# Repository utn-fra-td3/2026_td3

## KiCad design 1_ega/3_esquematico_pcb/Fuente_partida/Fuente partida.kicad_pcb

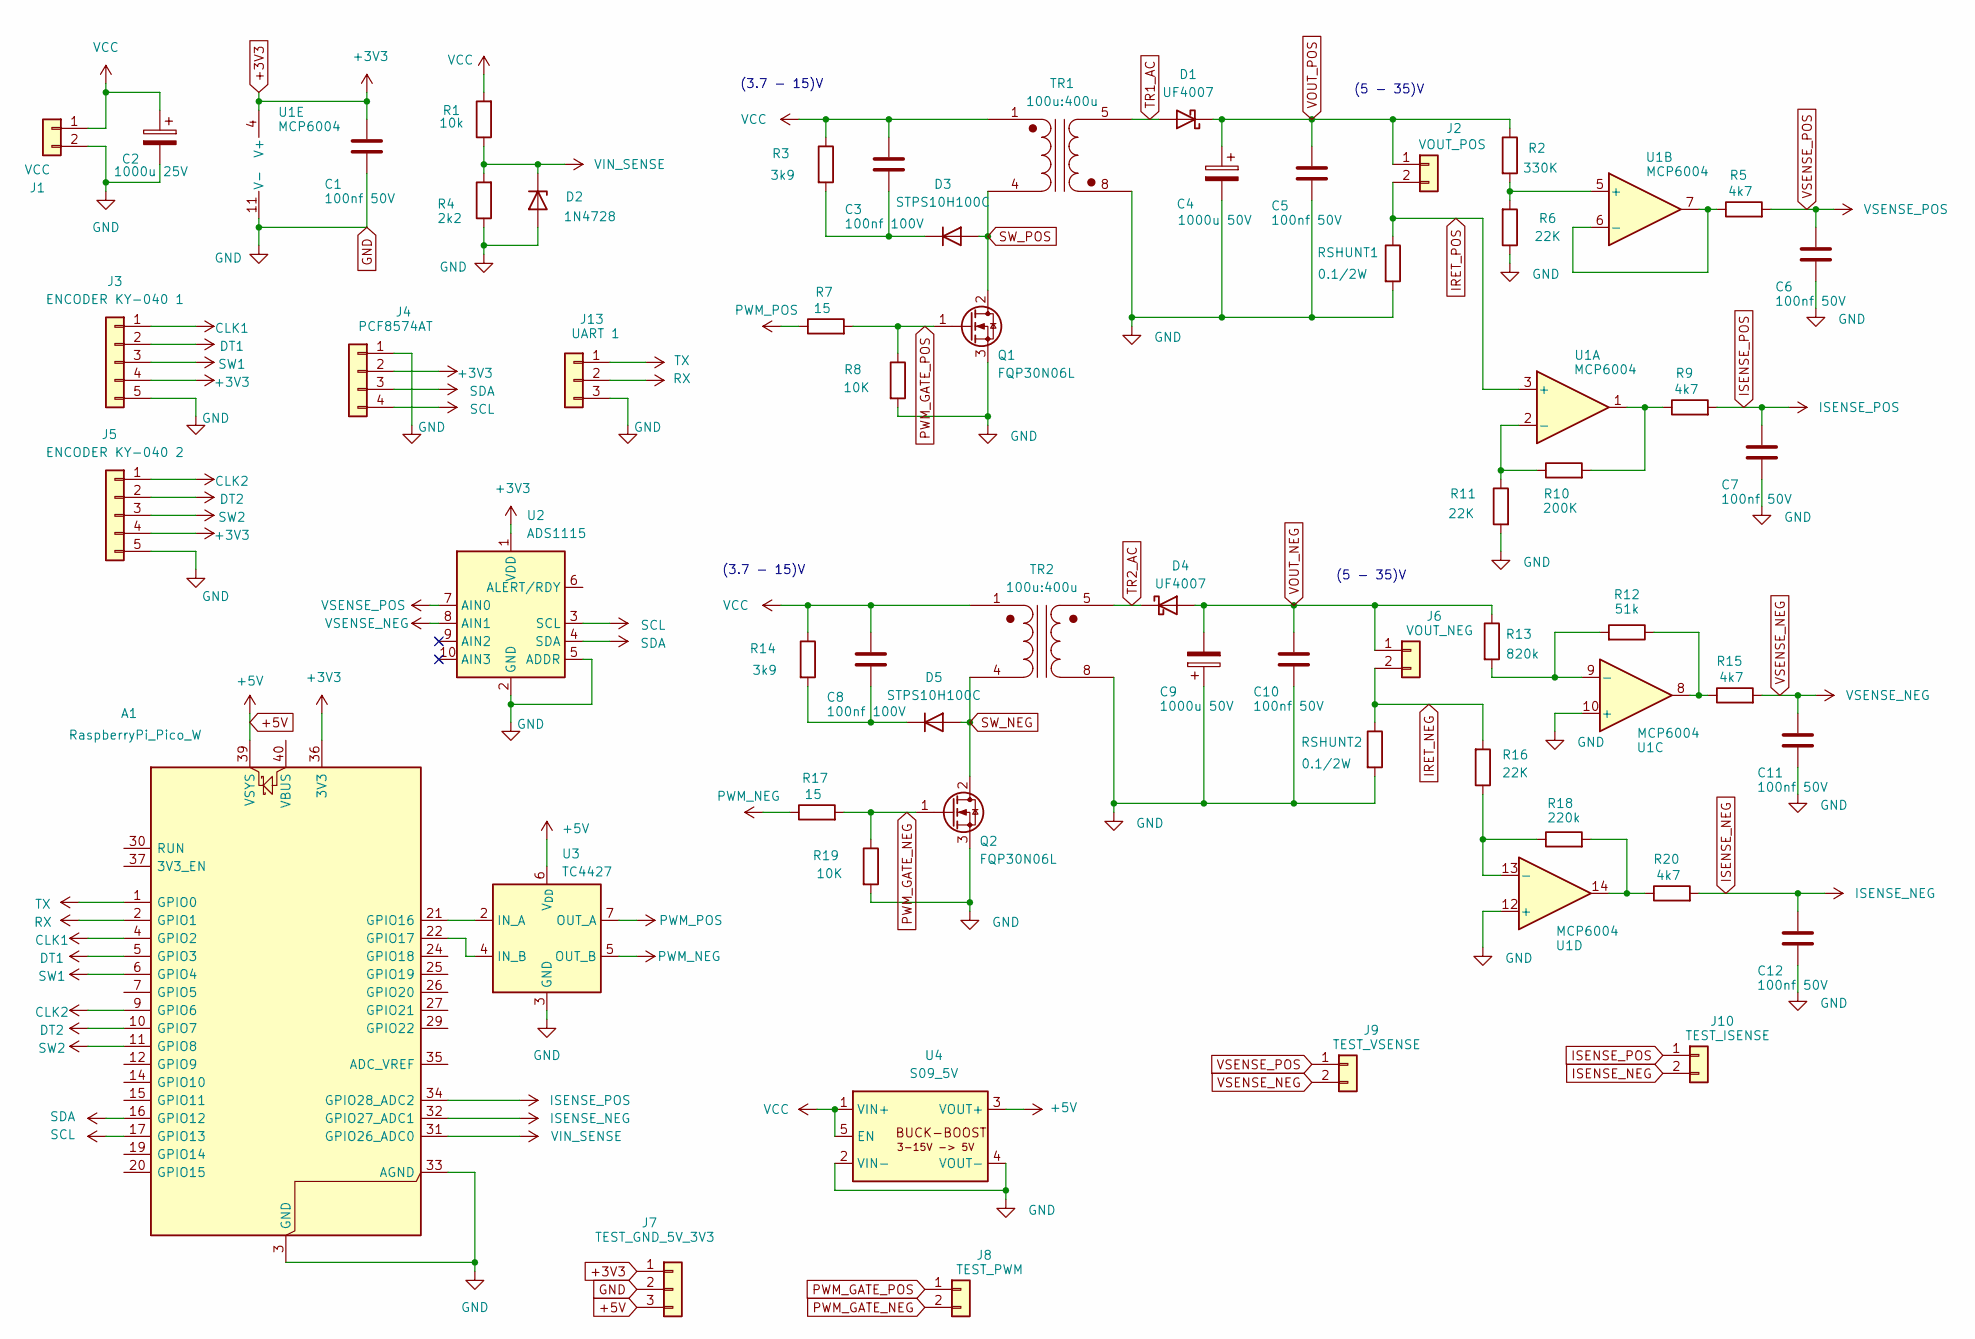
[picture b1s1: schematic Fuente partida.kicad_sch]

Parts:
A1: RaspberryPi_Pico_W; RaspberryPi_Pico_W_Pads_Anchos_Sin_Keepout_Antena
C1, C5, C6, C7, C10, C11, C12: 100nf 50V; C_Disc_D5.0mm_W2.5mm_P5.00mm
C2: 1000u 25V; CP_Radial_D10.0mm_P5.00mm
C3, C8: 100nf 100V; C_Disc_D5.0mm_W2.5mm_P5.00mm
C4, C9: 1000u 50V; CP_Radial_D16.0mm_P7.50mm
D1, D4: UF4007; D_DO-15_P10.16mm_Horizontal
D2: 1N4728; D_DO-41_SOD81_P10.16mm_Horizontal
D3, D5: STPS10H100C; D_DO-41_SOD81_P10.16mm_Horizontal
J1: VCC; TerminalBlock_MaiXu_MX126-5.0-02P_1x02_P5.00mm
J2: VOUT_POS; TerminalBlock_MaiXu_MX126-5.0-02P_1x02_P5.00mm
J3: ENCODER KY-040 1; PinSocket_1x05_P2.54mm_Vertical
J4: PCF8574AT; PinSocket_1x04_P2.54mm_Vertical
J5: ENCODER KY-040 2; PinSocket_1x05_P2.54mm_Vertical
J6: VOUT_NEG; TerminalBlock_MaiXu_MX126-5.0-02P_1x02_P5.00mm
J7: TEST_GND_5V_3V3; JST_XH_B3B-XH-A_1x03_P2.50mm_Vertical
J8: TEST_PWM; JST_XH_B2B-XH-A_1x02_P2.50mm_Vertical
J9: TEST_VSENSE; JST_XH_B2B-XH-A_1x02_P2.50mm_Vertical
J10: TEST_ISENSE; JST_XH_B2B-XH-A_1x02_P2.50mm_Vertical
J13: UART 1; PinSocket_1x03_P2.54mm_Vertical
Q1, Q2: FQP30N06L; TO-220-3_Vertical_P3.81mm
R1: 10k; R_Axial_DIN0204_L3.6mm_D1.6mm_P7.62mm_Horizontal
R2: 330K; R_Axial_DIN0204_L3.6mm_D1.6mm_P7.62mm_Horizontal
R3, R14: 3k9; R_Axial_DIN0204_L3.6mm_D1.6mm_P7.62mm_Horizontal
R4: 2k2; R_Axial_DIN0204_L3.6mm_D1.6mm_P7.62mm_Horizontal
R5, R9, R15, R20: 4k7; R_Axial_DIN0204_L3.6mm_D1.6mm_P7.62mm_Horizontal
R6, R11, R16: 22K; R_Axial_DIN0204_L3.6mm_D1.6mm_P7.62mm_Horizontal
R7, R17: 15; R_Axial_DIN0204_L3.6mm_D1.6mm_P7.62mm_Horizontal
R8, R19: 10K; R_Axial_DIN0204_L3.6mm_D1.6mm_P7.62mm_Horizontal
R10: 200K; R_Axial_DIN0204_L3.6mm_D1.6mm_P7.62mm_Horizontal
R12: 51k; R_Axial_DIN0204_L3.6mm_D1.6mm_P7.62mm_Horizontal
R13: 820k; R_Axial_DIN0204_L3.6mm_D1.6mm_P7.62mm_Horizontal
R18: 220k; R_Axial_DIN0204_L3.6mm_D1.6mm_P7.62mm_Horizontal
RSHUNT1, RSHUNT2: 0.1/2W; R_Axial_DIN0516_L15.5mm_D5.0mm_P7.62mm_Vertical
TR1, TR2: 100u:400u; Bobina_4P_30.5mm_P1_P4_P5_P8
U1: MCP6004; DIP-14_W7.62mm
U2: ADS1115; ADS1115_Modulo_1x10_Pads_Corregidos
U3: TC4427; DIP-8_W7.62mm
U4: S09_5V; S09_5V_BuckBoost_19x14mm

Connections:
+3V3: A1.36 (3V3), C1.1, J3.4, J4.2, J5.4, J7.1, U1.4 (V+), U2.1 (VDD)
+5V: A1.39 (VSYS), J7.3, U3.6 (V_{DD}), U4.3 (VOUT+)
CLK1: A1.4 (GPIO2), J3.1
CLK2: A1.9 (GPIO6), J5.1
DT1: A1.5 (GPIO3), J3.2
DT2: A1.10 (GPIO7), J5.2
GND: A1.3 (GND), A1.8 (GND), A1.13 (GND), A1.18 (GND), A1.23 (GND), A1.28 (GND), A1.33 (AGND), A1.38 (GND), C1.2, C2.2, C4.2, C5.2, C6.2, C7.2, C9.1, C10.2, C11.2, C12.2, D2.2 (A), J1.2, J3.5, J4.1, J5.5, J7.2, J13.3, Q1.3 (S), Q2.3 (S), R4.1, R6.1, R8.2, R11.2, R19.2, RSHUNT1.2, RSHUNT2.2, TR1.8 (SA), TR2.8 (SA), U1.10 (+), U1.11 (V-), U1.12 (+), U2.2 (GND), U2.5 (ADDR), U3.3 (GND), U4.2 (VIN-), U4.4 (VOUT-)
IRET_NEG: J6.2, R16.2, RSHUNT2.1
IRET_POS: J2.2, RSHUNT1.1, U1.3 (+)
ISENSE_NEG: A1.32 (GPIO27_ADC1), C12.1, J10.2, R20.2
ISENSE_POS: A1.34 (GPIO28_ADC2), C7.1, J10.1, R9.2
unnamed: A1.21 (GPIO16), U3.2 (IN_A)
unnamed: A1.22 (GPIO17), U3.4 (IN_B)
unnamed: C3.2, D3.1 (K), R3.2
unnamed: C8.2, D5.1 (K), R14.2
unnamed: R9.1, R10.2, U1.1
unnamed: R12.1, R15.1, U1.8
unnamed: R18.2, R20.1, U1.14
unnamed: R10.1, R11.1, U1.2 (-)
unnamed: R2.2, R6.2, U1.5 (+)
unnamed: R5.1, U1.6 (-), U1.7
unnamed: R12.2, R13.2, U1.9 (-)
unnamed: R16.1, R18.1, U1.13 (-)
PWM_GATE_NEG: J8.2, Q2.1 (G), R17.2, R19.1
PWM_GATE_POS: J8.1, Q1.1 (G), R7.2, R8.1
PWM_NEG: R17.1, U3.5 (OUT_B)
PWM_POS: R7.1, U3.7 (OUT_A)
RX: A1.2 (GPIO1), J13.2
SCL: A1.17 (GPIO13), J4.4, U2.3 (SCL)
SDA: A1.16 (GPIO12), J4.3, U2.4 (SDA)
SW1: A1.6 (GPIO4), J3.3
SW2: A1.11 (GPIO8), J5.3
SW_NEG: D5.2 (A), Q2.2 (D), TR2.4 (AB)
SW_POS: D3.2 (A), Q1.2 (D), TR1.4 (AB)
TR1_AC: D1.2 (A), TR1.5 (SB)
TR2_AC: D4.1 (K), TR2.5 (SB)
TX: A1.1 (GPIO0), J13.1
VCC: C2.1, C3.1, C8.1, J1.1, R1.2, R3.1, R14.1, TR1.1 (AA), TR2.1 (AA), U4.1 (VIN+), U4.5 (EN)
VIN_SENSE: A1.31 (GPIO26_ADC0), D2.1 (K), R1.1, R4.2
VOUT_NEG: C9.2, C10.1, D4.2 (A), J6.1, R13.1
VOUT_POS: C4.1, C5.1, D1.1 (K), J2.1, R2.1
VSENSE_NEG: C11.1, J9.2, R15.2, U2.8 (AIN1)
VSENSE_POS: C6.1, J9.1, R5.2, U2.7 (AIN0)

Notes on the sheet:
(5 - 35)V
(3.7 - 15)V

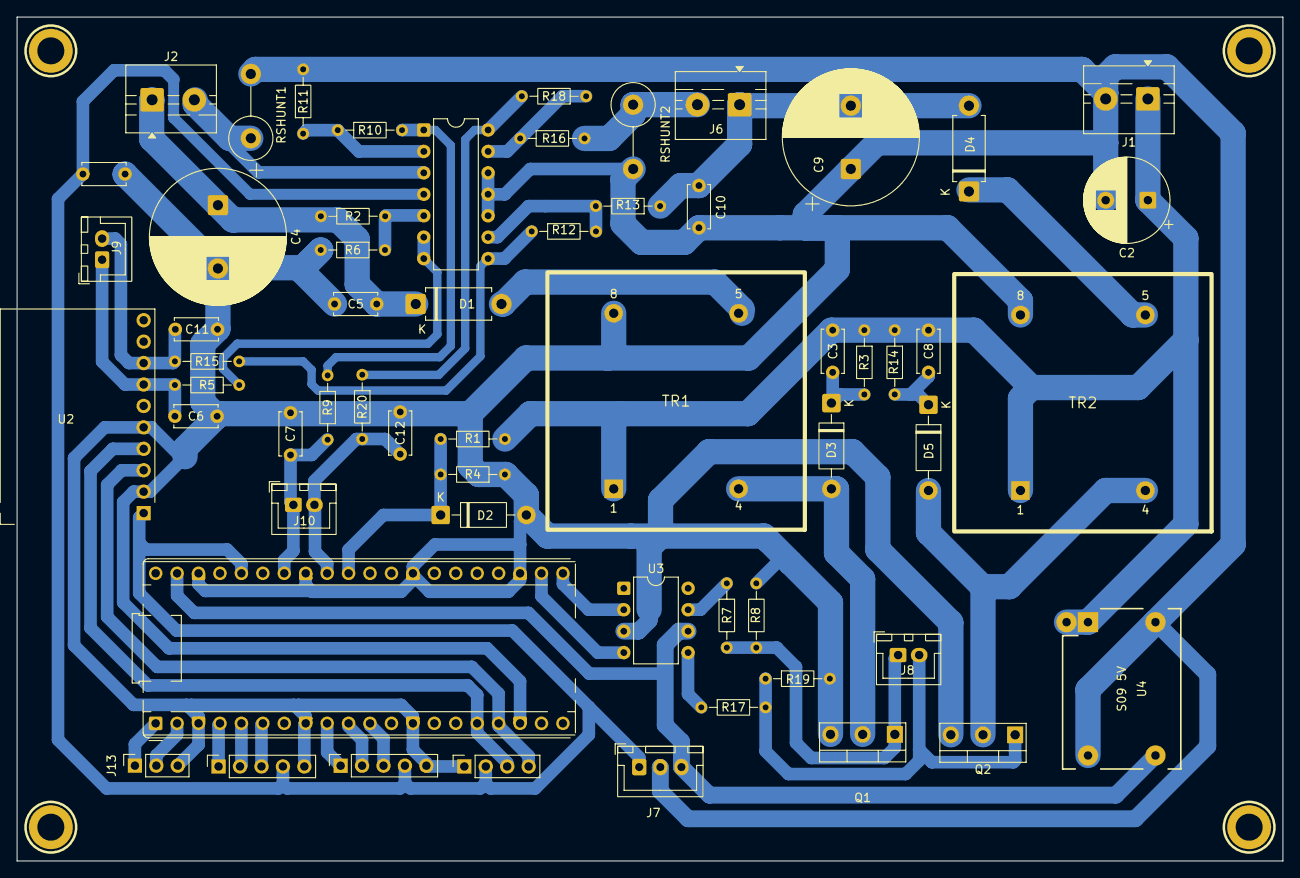
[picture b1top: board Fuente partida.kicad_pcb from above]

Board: 2 copper layers, 150.0 x 100.0 mm, 63 parts (0 on the bottom side), 43 nets.

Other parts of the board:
H1, H2, H3, H4: M3; MountingHole_3.2mm_M3_Pad_CNC

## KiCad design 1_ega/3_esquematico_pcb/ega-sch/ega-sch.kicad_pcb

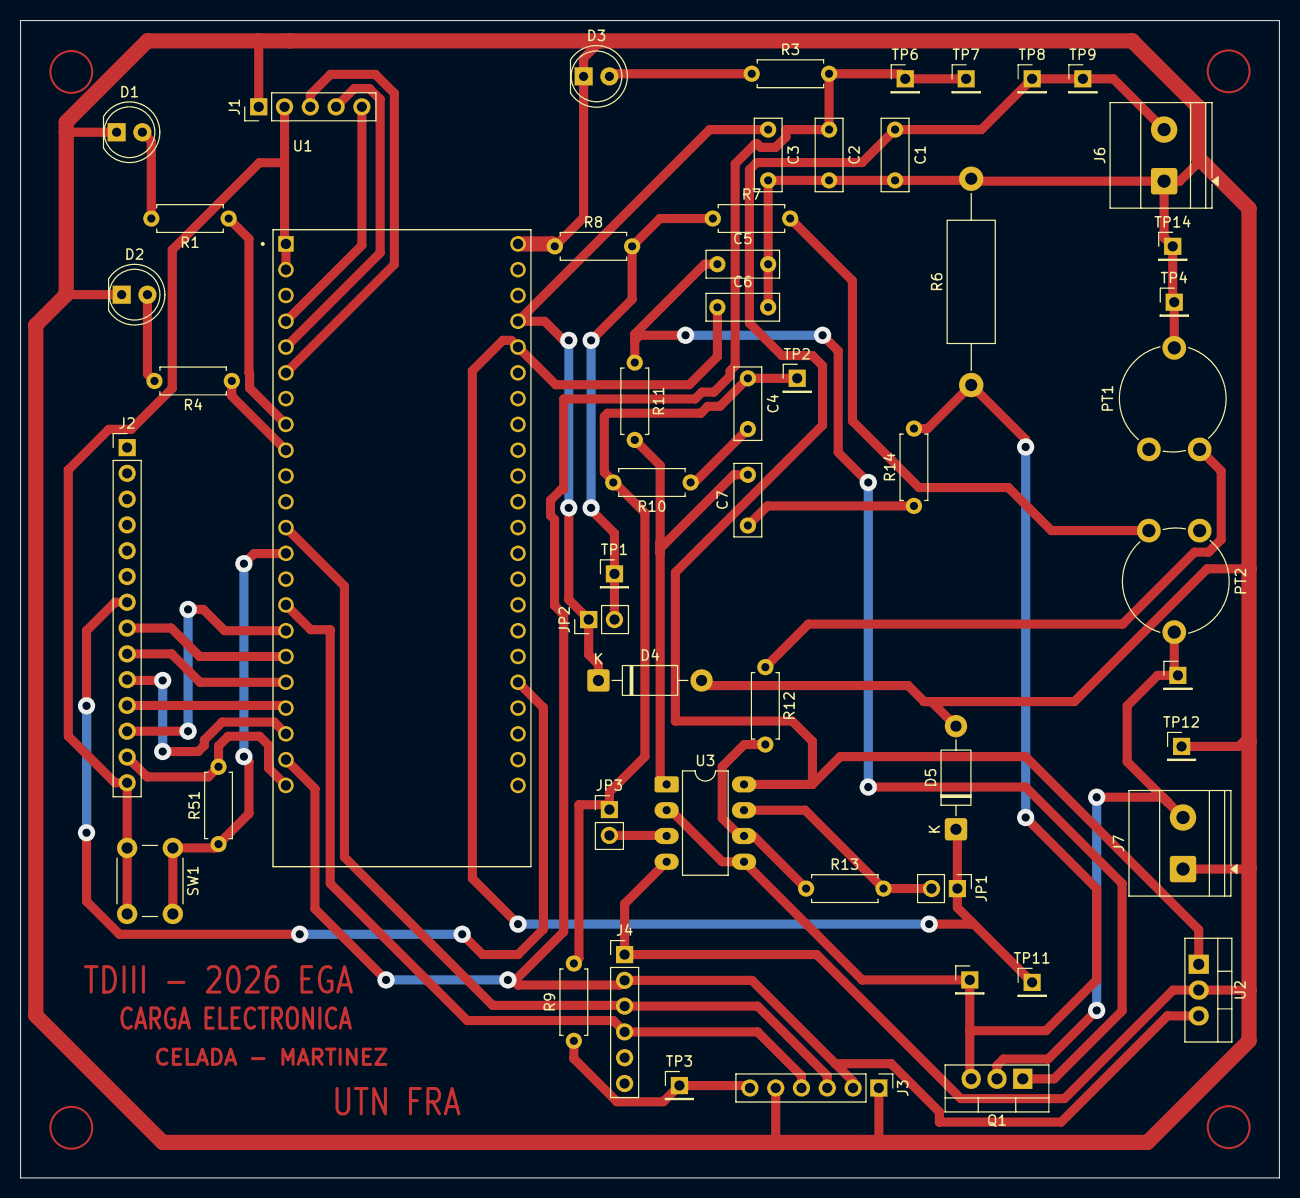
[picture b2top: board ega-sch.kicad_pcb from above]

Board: 2 copper layers, 124.0 x 114.0 mm, 54 parts (0 on the bottom side), 37 nets.

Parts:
C1, C2: 0,33uF; C_Disc_D7.0mm_W2.5mm_P5.00mm
C3, C4, C6: 100nF; C_Disc_D7.0mm_W2.5mm_P5.00mm
C5: 10nF; C_Disc_D7.0mm_W2.5mm_P5.00mm
C7: 1nF; C_Disc_D7.0mm_W2.5mm_P5.00mm
D1, D2: LD271; LED_D5.0mm_IRGrey
D3: ENCENDIDO; LED_D5.0mm_FlatTop
D4, D5: 1N4728A; D_DO-41_SOD81_P10.16mm_Horizontal
J1: Encoder; PinHeader_1x05_P2.54mm_Vertical
J2: TFT_Display; PinHeader_1x14_P2.54mm_Vertical
J3: MCP4725; PinHeader_1x06_P2.54mm_Vertical
J4: DS3231; PinHeader_1x06_P2.54mm_Vertical
J6: V+; TerminalBlock_Phoenix_MKDS-1,5-2-5.08_1x02_P5.08mm_Horizont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
J7: Ventrada; TerminalBlock_Phoenix_MKDS-1,5-2-5.08_1x02_P5.08mm_Horizont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
JP1, JP2, JP3: Jumper; PinHeader_1x02_P2.54mm_Vertical
PT1, PT2: PRESET 1K; Potentiometer_Piher_PT-10-V10_Vertical
Q1: IRFZ44; TO-220-3_Vertical
R1, R4: 330; R_Axial_DIN0207_L6.3mm_D2.5mm_P7.62mm_Horizontal
R3: 1K; R_Axial_DIN0207_L6.3mm_D2.5mm_P7.62mm_Horizontal
R6: Rshunt; R_Axial_DIN0414_L11.9mm_D4.5mm_P20.32mm_Horizontal
R7: 12K; R_Axial_DIN0207_L6.3mm_D2.5mm_P7.62mm_Horizontal
R8: 4,7K; R_Axial_DIN0207_L6.3mm_D2.5mm_P7.62mm_Horizontal
R9, R10, R12, R14, R51: 10K; R_Axial_DIN0207_L6.3mm_D2.5mm_P7.62mm_Horizontal
R11: 100; R_Axial_DIN0207_L6.3mm_D2.5mm_P7.62mm_Horizontal
R13: 3,3K; R_Axial_DIN0207_L6.3mm_D2.5mm_P7.62mm_Horizontal
SW1: SW_Push; SW_PUSH_6mm_H5mm
TP1: ADC_VIN; PinHeader_1x01_P2.54mm_Vertical
TP2: DAC; PinHeader_1x01_P2.54mm_Vertical
TP3: VDAC; PinHeader_1x01_P2.54mm_Vertical
TP4, TP14: GND; PinHeader_1x01_P2.54mm_Vertical
TP5: VIN; PinHeader_1x01_P2.54mm_Vertical
TP6, TP7: +5V; PinHeader_1x01_P2.54mm_Vertical
TP8, TP9: +12V; PinHeader_1x01_P2.54mm_Vertical
TP10: VSENS; PinHeader_1x01_P2.54mm_Vertical
TP11: ADC_VSENS; PinHeader_1x01_P2.54mm_Vertical
TP12: GND2; PinHeader_1x01_P2.54mm_Vertical
U1: ESP32-S3-DEVKITC-1-N16R8V; XCVR_ESP32-S3-DEVKITC-1-N16R8V
U2: LM7805_TO220; TO-220-3_Vertical
U3: LM358; DIP-8_W7.62mm_LongPads

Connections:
+3V3: J1.2, J2.14, SW1.2, U1.J1_1 (3V3), U1.J1_2 (3V3)
+5V: C2.1, J3.2, J4.2, R3.2, TP6.1, TP7.1, U1.J1_21 (5V0), U2.3 (VO)
+12V: C1.1, J6.2, TP8.1, TP9.1, U2.1 (VI), U3.8 (V+)
/Vin: J7.2, PT2.2, Q1.2 (D), TP5.1
ADC_VIN: C3.1, D4.1 (K), JP2.1 (A), U1.J3_4 (GPIO1)
ADC_VSENS: C6.1, D5.1 (K), JP1.1 (A), TP11.1, U1.J3_5 (GPIO2)
CLK: J1.5, U1.J1_4 (GPIO4)
DAC: J3.6, R9.1, TP3.1
DT: J1.4, U1.J1_5 (GPIO5)
GND: C1.2, C2.2, C3.2, C5.2, C6.2, D1.1 (K), D2.1 (K), D3.1 (K), D4.2 (A), D5.2 (A), J1.1, J2.13, J3.1, J3.5, J4.1, J6.1, J7.1, PT1.2, R6.2, R8.1, R51.2, TP4.1, TP12.1, TP14.1, U1.J1_22 (GND), U1.J3_1 (GND), U1.J3_21 (GND), U1.J3_22 (GND), U2.2 (GND), U3.4 (V-)
GND2: C4.2, R10.1
I2C0_SCL: J3.4, J4.4, U1.J1_15 (GPIO9)
I2C0_SDA: J3.3, J4.3, U1.J1_12 (GPIO8)
LED_MAX: R4.1, U1.J1_9 (GPIO16)
LED_MIN: R1.1, U1.J1_8 (GPIO15)
unnamed: C7.1, R14.1
unnamed: C7.2, R11.2, U3.1
unnamed: D1.2 (A), R1.2
unnamed: D2.2 (A), R4.2
unnamed: D3.2 (A), R3.1
unnamed: JP1.2 (B), R13.2, U3.7
unnamed: JP2.2 (B), R7.1, R8.2, TP1.1
unnamed: C4.1, JP3.1 (A), R9.2, R10.2, TP2.1
unnamed: JP3.2 (B), U3.3 (+)
unnamed: PT1.1, R12.1
unnamed: PT2.1, R7.2
unnamed: C5.1, Q1.1 (G), R11.1
unnamed: Q1.3 (S), R6.1, R14.2, TP10.1, U3.2 (-), U3.5 (+)
unnamed: R12.2, R13.1, U3.6 (-)
SW: J1.3, U1.J1_6 (GPIO6)
SW_CONFIG: R51.1, SW1.1, U1.J1_13 (GPIO3)
TFT_CS: J2.12, U1.J1_16 (GPIO10)
TFT_DC: J2.10, U1.J1_20 (GPIO14)
TFT_LED: J2.7, U1.J3_18 (GPIO21)
TFT_RESET: J2.11, U1.J1_19 (GPIO13)
TFT_SCK: J2.8, U1.J1_17 (GPIO11)
TFT_SDI: J2.9, U1.J1_18 (GPIO12)

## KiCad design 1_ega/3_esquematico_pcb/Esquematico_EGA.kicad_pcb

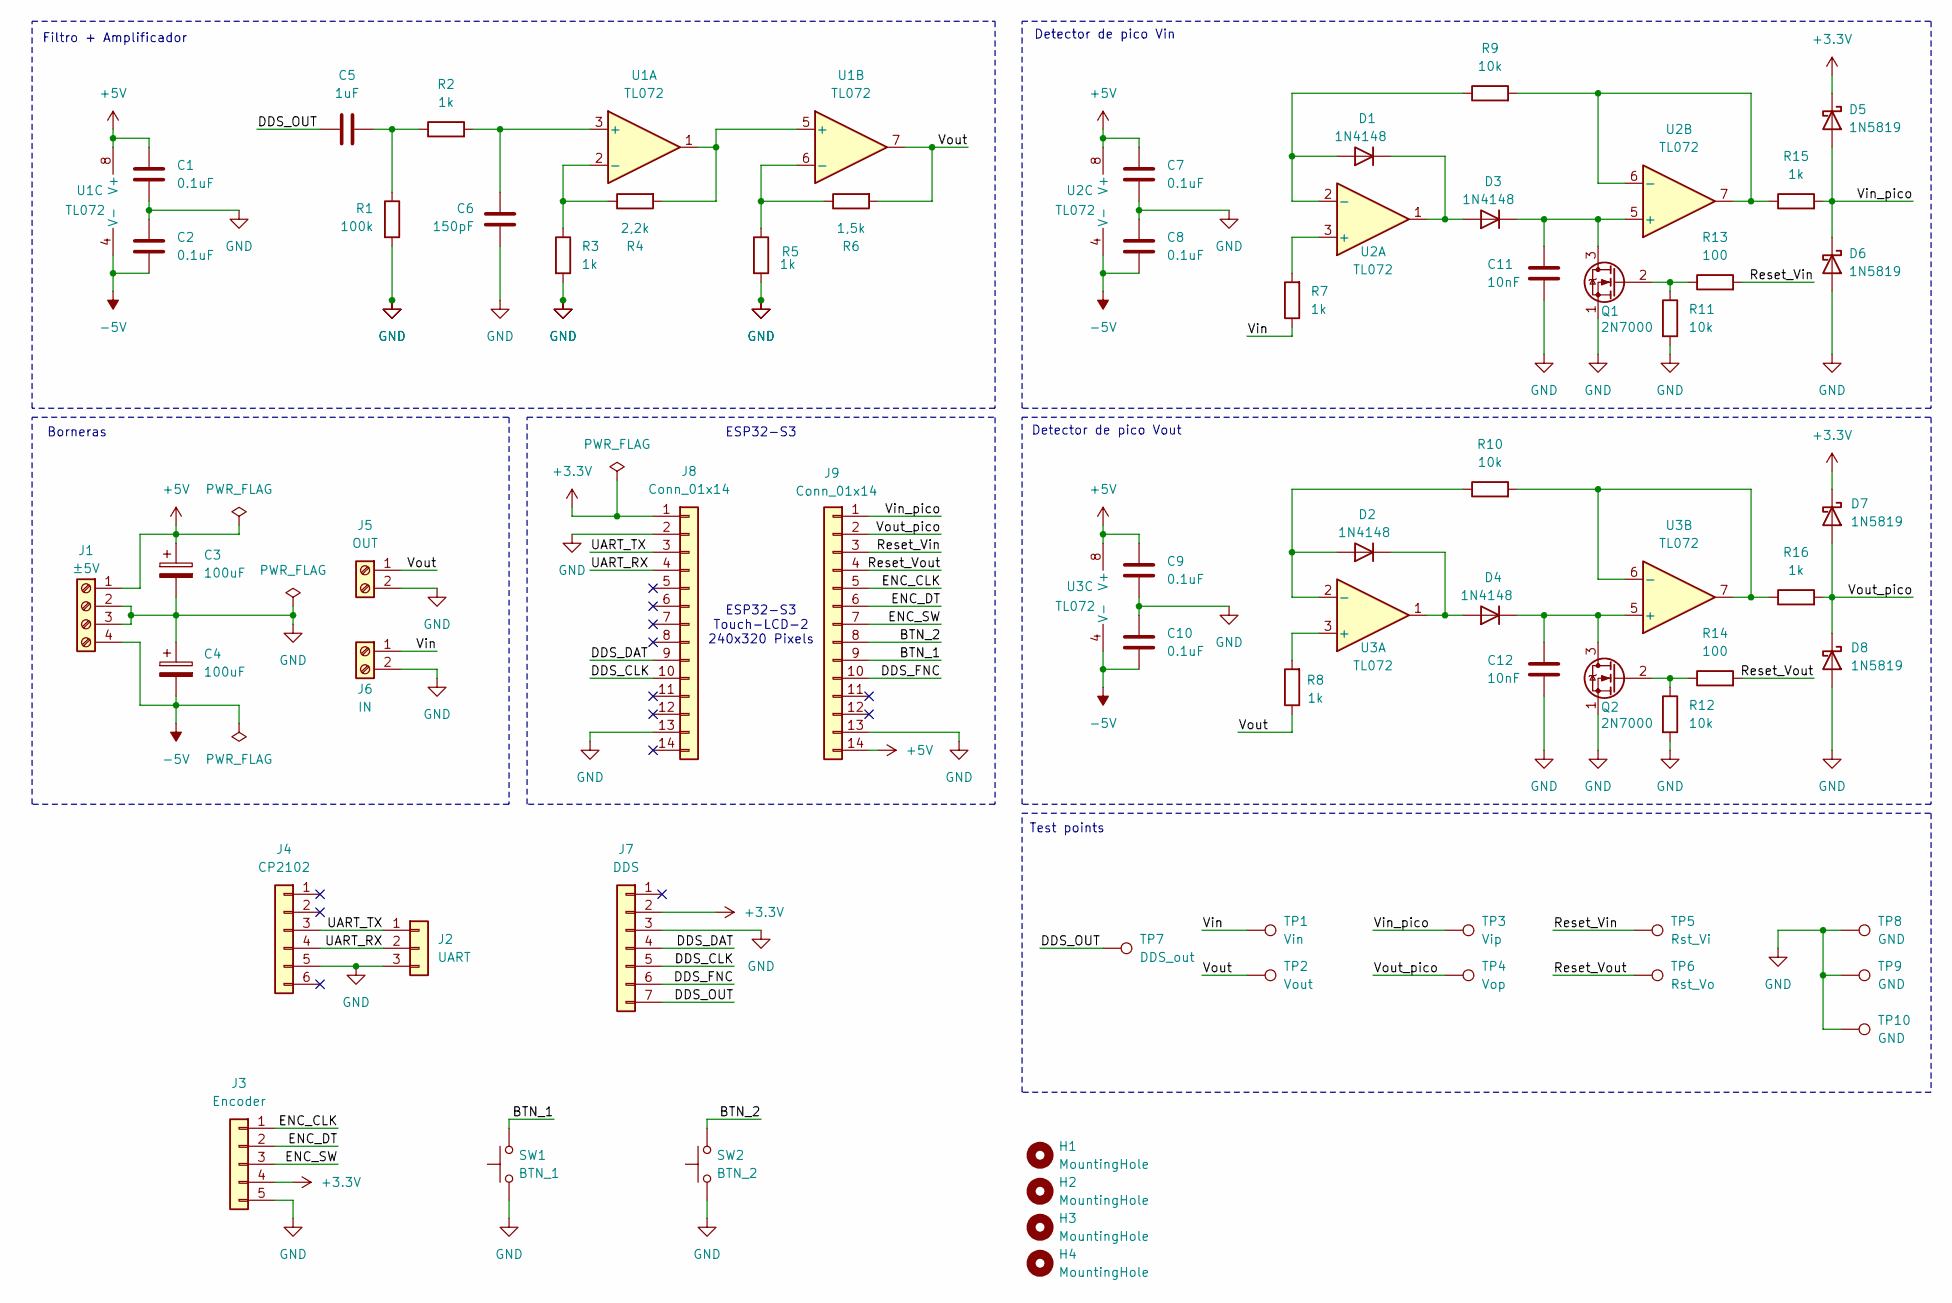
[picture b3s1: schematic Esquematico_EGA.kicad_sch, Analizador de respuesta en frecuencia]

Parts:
C1, C2, C7, C8, C9, C10: 0.1uF; C_Disc_D5.0mm_W2.5mm_P2.50mm
C3, C4: 100uF; CP_Radial_D7.5mm_P2.50mm
C5: 1uF; C_Disc_D5.0mm_W2.5mm_P5.00mm
C6: 150pF; C_Disc_D5.0mm_W2.5mm_P2.50mm
C11, C12: 10nF; C_Disc_D5.0mm_W2.5mm_P5.00mm
D1, D2, D3, D4: 1N4148; D_DO-35_SOD27_P7.62mm_Horizontal
D5, D6, D7, D8: 1N5819; D_DO-41_SOD81_P10.16mm_Horizontal
H1, H2, H3, H4: MountingHole; MountingHole_3.2mm_M3
J1: ±5V; TerminalBlock_Phoenix_MKDS-1,5-4-5.08_1x04_P5.08mm_Horizont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
J2: UART; PinSocket_1x03_P2.54mm_Vertical
J3: Encoder; PinSocket_1x05_P2.54mm_Vertical
J4: CP2102; PinSocket_1x06_P2.54mm_Vertical
J5: OUT; TerminalBlock_Phoenix_MKDS-1,5-2-5.08_1x02_P5.08mm_Horizont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
J6: IN; TerminalBlock_Phoenix_MKDS-1,5-2-5.08_1x02_P5.08mm_Horizont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
J7: DDS; PinSocket_1x07_P2.54mm_Vertical
J8, J9: Conn_01x14; PinSocket_1x14_P2.54mm_Vertical
Q1, Q2: 2N7000; TO-92_Inline_Wide
R1: 100k; R_Axial_DIN0207_L6.3mm_D2.5mm_P10.16mm_Horizontal
R2, R3, R5, R7, R8, R15, R16: 1k; R_Axial_DIN0207_L6.3mm_D2.5mm_P10.16mm_Horizontal
R4: 2,2k; R_Axial_DIN0207_L6.3mm_D2.5mm_P10.16mm_Horizontal
R6: 1,5k; R_Axial_DIN0207_L6.3mm_D2.5mm_P10.16mm_Horizontal
R9, R10, R11, R12: 10k; R_Axial_DIN0207_L6.3mm_D2.5mm_P10.16mm_Horizontal
R13, R14: 100; R_Axial_DIN0207_L6.3mm_D2.5mm_P10.16mm_Horizontal
SW1: BTN_1; SW_PUSH_6mm_H5mm
SW2: BTN_2; SW_PUSH_6mm_H5mm
TP1: Vin; PinHeader_1x01_P2.54mm_Vertical
TP2: Vout; PinHeader_1x01_P2.54mm_Vertical
TP3: Vip; PinHeader_1x01_P2.54mm_Vertical
TP4: Vop; PinHeader_1x01_P2.54mm_Vertical
TP5: Rst_Vi; PinHeader_1x01_P2.54mm_Vertical
TP6: Rst_Vo; PinHeader_1x01_P2.54mm_Vertical
TP7: DDS_out; PinHeader_1x01_P2.54mm_Vertical
TP8, TP9, TP10: GND; PinHeader_1x01_P2.54mm_Vertical
U1, U2, U3: TL072; DIP-8_W7.62mm_LongPads

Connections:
+3.3V: D5.1 (K), D7.1 (K), J3.4, J7.2, J8.1
+5V: C1.1, C3.1, C7.1, C9.1, J1.1, J9.14, U1.8 (V+), U2.8 (V+), U3.8 (V+)
-5V: C2.2, C4.2, C8.2, C10.2, J1.4, U1.4 (V-), U2.4 (V-), U3.4 (V-)
/BTN_1: J9.9, SW1.2
/BTN_2: J9.8, SW2.2
/DDS_CLK: J7.5, J8.10
/DDS_DAT: J7.4, J8.9
/DDS_FNC: J7.6, J9.10
/DDS_OUT: C5.1, J7.7, TP7.1 (1_1)
/ENC_CLK: J3.1, J9.5
/ENC_DT: J3.2, J9.6
/ENC_SW: J3.3, J9.7
/Reset_Vin: J9.3, R13.2, TP5.1 (1_1)
/Reset_Vout: J9.4, R14.2, TP6.1 (1_1)
/UART_RX: J2.2, J4.4, J8.4
/UART_TX: J2.1, J4.3, J8.3
/Vin: J6.1, R7.1, TP1.1 (1_1)
/Vin_pico: D5.2 (A), D6.1 (K), J9.1, R15.2, TP3.1 (1_1)
/Vout: J5.1, R6.2, R8.1, TP2.1 (1_1), U1.7
/Vout_pico: D7.2 (A), D8.1 (K), J9.2, R16.2, TP4.1 (1_1)
GND: C1.2, C2.1, C3.2, C4.1, C6.2, C7.2, C8.1, C9.2, C10.1, C11.2, C12.2, D6.2 (A), D8.2 (A), J1.2, J1.3, J2.3, J3.5, J4.5, J5.2, J6.2, J7.3, J8.2, J8.13, J9.13, Q1.1 (S), Q2.1 (S), R1.2, R3.2, R5.2, R11.2, R12.2, SW1.1, SW2.1, TP8.1 (1_1), TP9.1 (1_1), TP10.1 (1_1)
unnamed: C5.2, R1.1, R2.1
unnamed: D1.2 (A), R9.1, U2.2 (-)
unnamed: D1.1 (K), D3.2 (A), U2.1
unnamed: D2.2 (A), R10.1, U3.2 (-)
unnamed: D2.1 (K), D4.2 (A), U3.1
unnamed: C11.1, D3.1 (K), Q1.3 (D), U2.5 (+)
unnamed: C12.1, D4.1 (K), Q2.3 (D), U3.5 (+)
unnamed: Q1.2 (G), R11.1, R13.1
unnamed: Q2.2 (G), R12.1, R14.1
unnamed: C6.1, R2.2, U1.3 (+)
unnamed: R3.1, R4.1, U1.2 (-)
unnamed: R4.2, U1.1, U1.5 (+)
unnamed: R5.1, R6.1, U1.6 (-)
unnamed: R7.2, U2.3 (+)
unnamed: R9.2, R15.1, U2.6 (-), U2.7
unnamed: R8.2, U3.3 (+)
unnamed: R10.2, R16.1, U3.6 (-), U3.7

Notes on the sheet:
Filtro + Amplificador
ESP32-S3
Borneras
Detector de pico Vout
ESP32-S3 Touch-LCD-2 240x320 Pixels
Test points
Detector de pico Vin

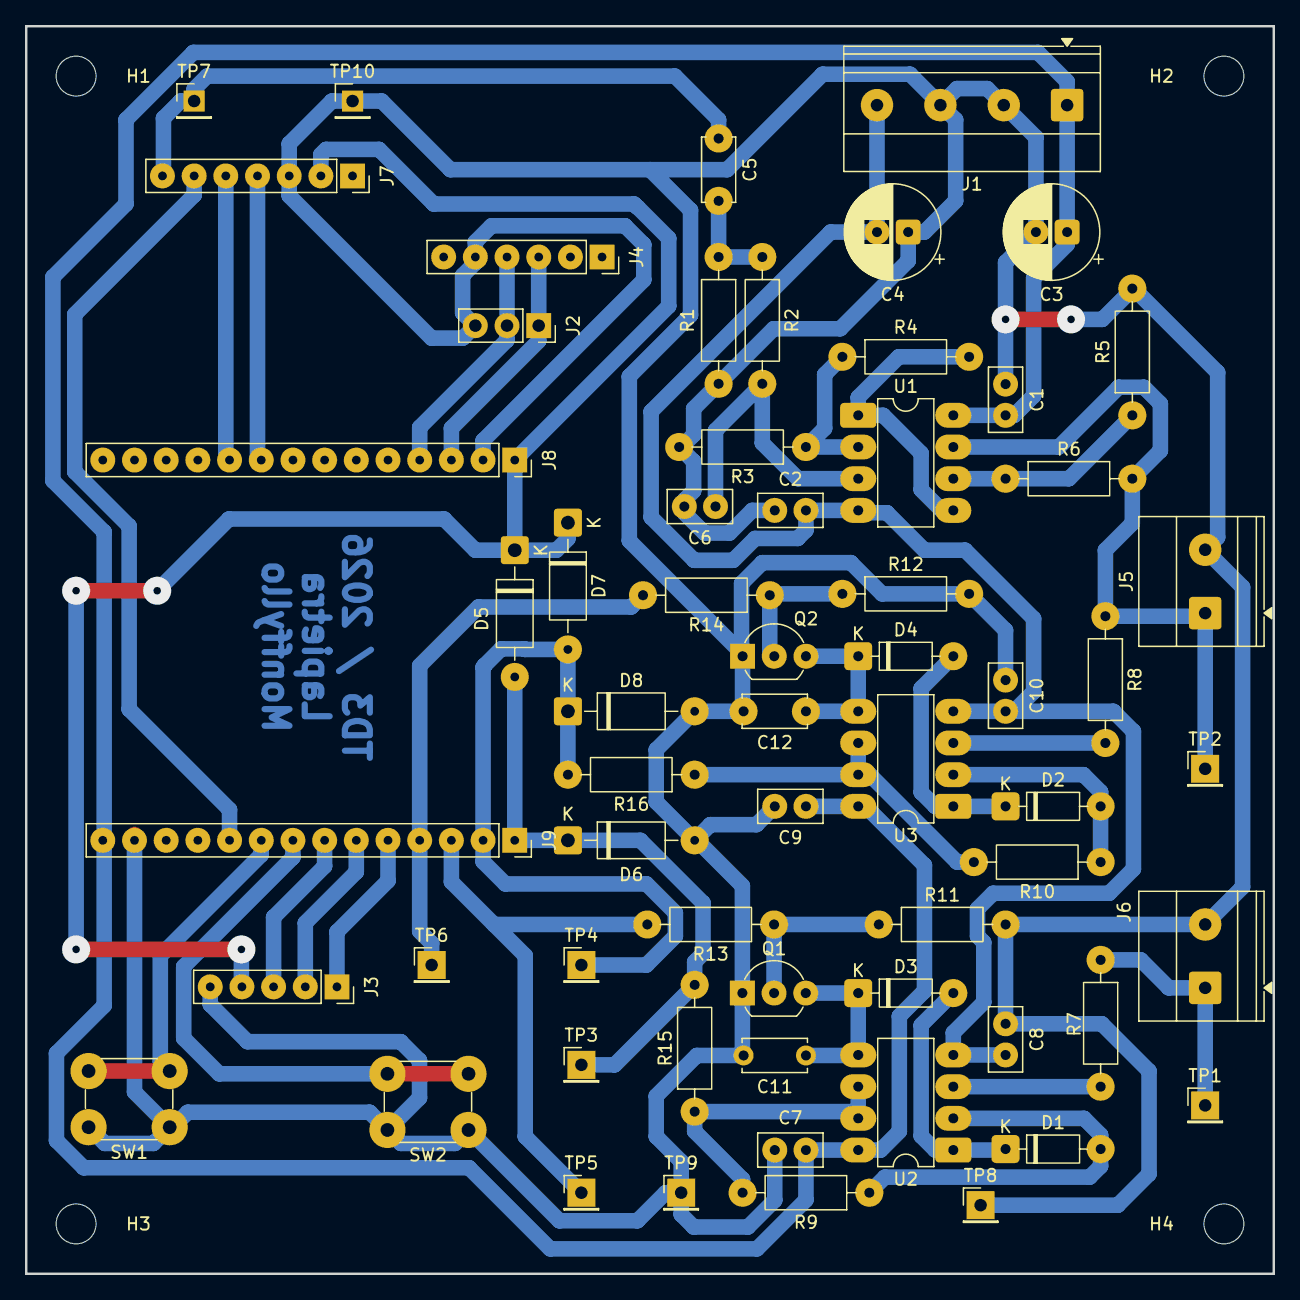
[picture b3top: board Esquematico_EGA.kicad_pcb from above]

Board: 2 copper layers, 100.0 x 100.0 mm, 66 parts (0 on the bottom side), 38 nets.

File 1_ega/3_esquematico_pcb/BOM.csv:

"Reference","Qty","Value","Footprint"
"C1,C2,C7,C8,C9,C10","6","0.1uF","Capacitor_THT:C_Disc_D5.0mm_W2.5mm_P2.50mm"
"C3,C4","2","100uF","Capacitor_THT:CP_Radial_D7.5mm_P2.50mm"
"C5","1","1uF","Capacitor_THT:C_Disc_D5.0mm_W2.5mm_P5.00mm"
"C6","1","150pF","Capacitor_THT:C_Disc_D5.0mm_W2.5mm_P2.50mm"
"C11,C12","2","10uF","Capacitor_THT:C_Disc_D5.0mm_W2.5mm_P5.00mm"
"D1,D2,D3,D4","4","1N4148","Diode_THT:D_DO-35_SOD27_P7.62mm_Horizontal"
"D5,D6,D7,D8","4","1N5819","Diode_THT:D_DO-41_SOD81_P10.16mm_Horizontal"
"J1","1","±5V","TerminalBlock_Phoenix:TerminalBlock_Phoenix_MKDS-1,5-4-5.08_1x04_P5.08mm_Horizontal"
"J2","1","UART","Connector_PinSocket_2.54mm:PinSocket_1x03_P2.54mm_Vertical"
"J3","1","Encoder","Connector_PinSocket_2.54mm:PinSocket_1x05_P2.54mm_Vertical"
"J4","1","CP2102","Connector_PinSocket_2.54mm:PinSocket_1x06_P2.54mm_Vertical"
"J5","1","OUT","TerminalBlock_Phoenix:TerminalBlock_Phoenix_MKDS-1,5-2-5.08_1x02_P5.08mm_Horizontal"
"J6","1","IN","TerminalBlock_Phoenix:TerminalBlock_Phoenix_MKDS-1,5-2-5.08_1x02_P5.08mm_Horizontal"
"J7","1","DDS","Connector_PinSocket_2.54mm:PinSocket_1x07_P2.54mm_Vertical"
"J8,J9","2","Conn_01x14","Connector_PinSocket_2.54mm:PinSocket_1x14_P2.54mm_Vertical"
"Q1,Q2","2","2N7000","Package_TO_SOT_THT:TO-92_Inline_Wide"
"R1","1","100k","Resistor_THT:R_Axial_DIN0207_L6.3mm_D2.5mm_P10.16mm_Horizontal"
"R2,R3,R5,R7,R8,R15,R16","7","1k","Resistor_THT:R_Axial_DIN0207_L6.3mm_D2.5mm_P10.16mm_Horizontal"
"R4","1","2,2k","Resistor_THT:R_Axial_DIN0207_L6.3mm_D2.5mm_P10.16mm_Horizontal"
"R6","1","1,5k","Resistor_THT:R_Axial_DIN0207_L6.3mm_D2.5mm_P10.16mm_Horizontal"
"R9,R10,R11,R12","4","10k","Resistor_THT:R_Axial_DIN0207_L6.3mm_D2.5mm_P10.16mm_Horizontal"
"R13,R14","2","100","Resistor_THT:R_Axial_DIN0207_L6.3mm_D2.5mm_P10.16mm_Horizontal"
"SW1","1","BTN_1","Button_Switch_THT:SW_PUSH_6mm_H5mm"
"SW2","1","BTN_2","Button_Switch_THT:SW_PUSH_6mm_H5mm"
"TP1","1","Vin","Connector_PinHeader_2.54mm:PinHeader_1x01_P2.54mm_Vertical"
"TP2","1","Vout","Connector_PinHeader_2.54mm:PinHeader_1x01_P2.54mm_Vertical"
"TP3","1","Vip","Connector_PinHeader_2.54mm:PinHeader_1x01_P2.54mm_Vertical"
"TP4","1","Vop","Connector_PinHeader_2.54mm:PinHeader_1x01_P2.54mm_Vertical"
"TP5","1","Rst_Vi","Connector_PinHeader_2.54mm:PinHeader_1x01_P2.54mm_Vertical"
"TP6","1","Rst_Vo","Connector_PinHeader_2.54mm:PinHeader_1x01_P2.54mm_Vertical"
"TP7","1","DDS_out","Connector_PinHeader_2.54mm:PinHeader_1x01_P2.54mm_Vertical"
"TP8,TP9,TP10","3","GND","Connector_PinHeader_2.54mm:PinHeader_1x01_P2.54mm_Vertical"
"U1,U2,U3","3","TL072","Package_DIP:DIP-8_W7.62mm_LongPads"

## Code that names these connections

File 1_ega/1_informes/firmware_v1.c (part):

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#define PIN_SPI_CLK      14
#define PIN_SPI_CS       15

#define PIN_ENC_CLK      18
#define PIN_ENC_DT       5
#define PIN_ENC_SW       19   // Botón Encoder: Cambia el PASO de frecuencia
#define PIN_BOTON_MODO   4    // Botón Extra: Cambia la FORMA de onda

#define PIN_I2C_SCL      22
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// UART Configuración (Nativa para Comandos Remotos)
#define UART_PORT_NUM      UART_NUM_0
#define UART_BUF_SIZE      1024
#define PIN_UART_TX        UART_PIN_NO_CHANGE
#define PIN_UART_RX        UART_PIN_NO_CHANGE

// Parámetros DDS
#define SAMPLING_FREQ      25000      
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static void IRAM_ATTR encoder_gpio_isr_handler(void* arg) {
    uint32_t tiempo_actual = esp_timer_get_time();
    if (tiempo_actual - ultimo_tiempo_enc_isr > 35000) { // Debounce 35ms
        int nivel_dt = gpio_get_level(PIN_ENC_DT);
        if (nivel_dt == 1) {
            if (frecuencia_actual + paso_frecuencia <= 20000) frecuencia_actual += paso_frecuencia;
            else frecuencia_actual = 20000;
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        ultimo_modo = ext_btn;

        // --- Monitorear Botón Paso (GPIO 19) ---
        int enc_btn = gpio_get_level(PIN_ENC_SW);
        if (ultimo_sw == 1 && enc_btn == 0) {
            vTaskDelay(pdMS_TO_TICKS(40)); 
            if (gpio_get_level(PIN_ENC_SW) == 0) {
                if (paso_frecuencia == 1)        paso_frecuencia = 10;
                else if (paso_frecuencia == 10)  paso_frecuencia = 100;
                else if (paso_frecuencia == 100) paso_frecuencia = 1000;
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
    // F. Entradas Digitales e Interrupción por hardware del Encoder
    gpio_config_t enc_cfg = { 
        .pin_bit_mask = (1ULL << PIN_ENC_CLK) | (1ULL << PIN_ENC_DT), 
        .mode = GPIO_MODE_INPUT, 
        .pull_up_en = GPIO_PULLUP_ENABLE, 
        .pull_down_en = GPIO_PULLDOWN_DISABLE, 
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    ESP_ERROR_CHECK(gpio_config(&enc_cfg)); 

    gpio_config_t botones_cfg = { 
        .pin_bit_mask = (1ULL << PIN_ENC_SW) | (1ULL << PIN_BOTON_MODO), 
        .mode = GPIO_MODE_INPUT, 
        .pull_up_en = GPIO_PULLUP_ENABLE, 
        .pull_down_en = GPIO_PULLDOWN_DISABLE, 
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    if (err_isr != ESP_OK && err_isr != ESP_ERR_INVALID_STATE) {
        ESP_LOGE(TAG, "Fallo al inicializar servicio ISR");
    }
    ESP_ERROR_CHECK(gpio_isr_handler_add(PIN_ENC_CLK, encoder_gpio_isr_handler, NULL));

    // G. Inicializar Conductor UART0
    uart_config_t uart_config = {
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    };
    ESP_ERROR_CHECK(uart_driver_install(UART_PORT_NUM, UART_BUF_SIZE * 2, 0, 0, NULL, 0));
    ESP_ERROR_CHECK(uart_param_config(UART_PORT_NUM, &uart_config));
    ESP_ERROR_CHECK(uart_set_pin(UART_PORT_NUM, PIN_UART_TX, PIN_UART_RX, UART_PIN_NO_CHANGE, UART_PIN_NO_CHANGE));

    // H. Inicializar Conductor I2C Maestro para OLED (v6.0)
    i2c_master_bus_config_t i2c_bus_config = { .clk_source = I2C_CLK_SRC_DEFAULT, .i2c_port = I2C_NUM_0, .scl_io_num = PIN_I2C_SCL, .sda_io_num = PIN_I2C_SDA, .glitch_ignore_cnt = 7, .flags.enable_internal_pullup = true };
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
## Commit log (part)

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2025-07-03 perf: soporte para custom FreeRTOSConfig desde aplicacion y mejora de definicion de rutas de acuerdo a arquitectura
2025-07-03 feat: soporte para picow
2025-07-03 chore: elimino tarea de inicializacion
2025-07-03 chore: detalle estetico del CMakeLists
2025-07-03 chore: elimino tarea de init
2025-07-03 chore: elimino tarea init
2025-07-03 chore: detalle estetico en inclusion de archivo
2025-07-03 chore: elimino tarea de init y doy soporte a picow
2025-07-03 chore: instruccion mas generica
2025-07-03 chore: mejoro inclusion de freertos
2025-07-03 feat: ejemplo de software timers
2025-07-03 docs: instrucciones sobre biblioteca de freertos
2025-07-03 docs: documentacion sobre cada definicion de freertos
2025-07-03 perf: habilita eleccion de heap
2025-07-03 chore: aclaración sobre personalización de freertos
2025-07-03 docs: actualización de referencias a manuales de FreeRTOS
2025-07-04 feat: ejemplo de static blinky
2025-07-04 perf: flexibilizacion sobre el uso de configuracion de usuario
2025-07-04 docs: documentacion de uso de configuracion de usuario
2025-07-04 chore: elimino contenido erroneo sobre inclusion de freertos
2025-07-04 chore: instruccion de cmake como en la documentacion
2025-07-04 chore: instrucciones de cmake actualizadas a las de la documentacion
2025-07-04 chore: readme de los proyectos
2025-07-04 feat: ejemplo de software timer estatico
2025-07-04 docs: manual de freertos de richard barry
2025-07-04 docs: ejemplos linkeados y ordenados por unidades
2025-07-04 feat: ejemplo de static queue
2025-07-04 chore: arreglo del titulo
2025-07-04 chore: agrego referencia a ejemplo
2025-07-16 feat: ejemplos de gpos
2025-07-16 docs: listado de ejemplos
2025-07-18 feat: soporte para abstraccion de hardware para el GPIO
2025-07-18 chore: ignoro directorio de build
2025-07-18 docs: consigna de TP5
2025-07-18 chore: makefile de guia
2025-07-18 chore: template de guia
2025-07-19 chore: setup basico
2025-09-15 docs: apuntes de clase de unidad 3
2025-09-15 docs: bibliografia unidad 3
2025-09-15 chore: readmes de unidades tematicas
2025-09-15 docs: apuntes de clase de unidad 4
2025-09-15 docs: bibliografia de linux embebido
2025-09-22 docs: presentacion de intro a linux
2025-10-24 chore: directorio y contenido de egb
2026-03-18 docs: libro linux embebido
2026-03-18 docs: apunte gpos
2026-06-01 Agrego Diagram en Bloques
2026-06-01 docs: diagrama de tareas y de bloques
2026-06-01 docs: diagramas de tareas y de bloques
2026-06-01 Adjunto diagrama en bloques
2026-06-01 Adicion de diagramas de tareas y de bloques v1
2026-06-01 Adicion diagramas
2026-06-01 primer entrega EGA
2026-06-02 Entrega Diagrama en bloques y de tareas
2026-06-02 Entrega1
2026-06-02 fix diagrama de tareas
2026-06-02 Primer entrega EGA1
2026-06-03 Subiendo diagramas
2026-06-03 agrego diagrama de tareas
2026-06-03 agrego diagrama en bloques
2026-06-03 Se agrega mapa de tareas y esquema
2026-06-03 agrego diagrama de tareas y bloques
2026-06-03 Se agregan diagramas .png
2026-06-03 Se borran archivos .pdf
2026-06-03 agrego diagrama de tareas (corregido) y bloques
2026-06-03 Entrega de mapa de tareas y diagrama en bloques
2026-06-03 diagrama de bloques
2026-06-03 diagrama en bloques
2026-06-03 Subiendo los diagramas
2026-06-03 diagrama de tareas
2026-06-03 Revert "Merge branch 'utn-fra-td3:main' into ega/v1"
    This reverts commit 921fad73fec5d0f6647a61cc478a1ee40666025a, reversing
    changes made to 96e932683d5ec393eb53ed42fafc01d03bc4ec54.
2026-06-03 Entrega de mapa de tareas corregido
2026-06-03 Primer entrega EGA
    Entrega de diagrama de conexion y diagrama de tareas de carga electronica
2026-06-04 docs: add task diagram
2026-06-04 docs: add conection diagram
2026-06-04 agregar ega.pdf
2026-06-04 Agregar .gitignore del workspace
2026-06-04 Agregar referencias del AD9833 y ESP32-S3
2026-06-04 Eliminar carpeta freertos del workspace
2026-06-04 Se actualizo diagrama en bloques y se agrego diagrama de tareas.
2026-06-04 estructura inicial del proyecto
2026-06-05 Se actualiza el diagrama en bloques y se carga el diagrama de tareas
2026-06-05 chore: agregar archivos 1_informes
2026-06-05 chore: agregar pcb kicad
2026-06-05 chore: agregar informes ega
2026-06-05 chore: agregar pcb inicio
2026-06-06 display funcionando con LVGL
2026-06-06 flash size 16MB
2026-06-06 integrar UI generada por SquareLine Studio
2026-06-06 touch CST816S funcionando
2026-06-07 agregar fuente RobotoMono 14px con caracteres en español
2026-06-08 correccion de diagramas.
2026-06-08 Diagramas ADC integrado y datasheets
2026-06-08 ADC con lectura one shoot
2026-06-08 adicion de interrupciones y tarea interfaz.
2026-06-08 entrega informe preliminar
2026-06-08 Adjunto Preliminar
2026-06-08 add informe preliminar
2026-06-08 vuelvo a subir lo mismo pero en formato png
2026-06-08 vuelvo a subir lo mismo en formato png
2026-06-09 redirigir console a USB Serial/JTAG para separar logs de UART0
2026-06-09 chore:se agrega informe preliminar ega
2026-06-09 implementar recepción de comandos UART por línea
2026-06-10 Subiendo informe preliminar
2026-06-10 Agrego proyecto SquareLine
2026-06-10 Entrega de informe preliminar
2026-06-11 agrego preinforme
2026-06-11 pre informe Generador de señales. Gutierrez-Caceres
2026-06-11 Se sube preliminar
2026-06-11 Agrego informe Preliminar
2026-06-11 Informe Preliminar
2026-06-11 Entrega informe EGA
2026-06-15 Informe final
2026-06-15 Informe IEEE
2026-06-15 Creacion de tareas y codigo.
2026-06-16 esquematico y pcb
2026-06-16 simulaciones LTSpice
2026-06-16 borrar archivos temporales
2026-06-16 actualizar diagrama en bloques
2026-06-16 agrego task_sweep adc uart nvs task_menu
2026-06-17 añadir referencias esp32-s3 y opamp
2026-06-17 agregar imagenes de simulacion
2026-06-17 driver CP2102 para windows
2026-06-17 ad9833 funcionando para generar senoidales
2026-06-17 agregar inicializacion de NVS en task_nvs
2026-06-17 Subiendo codigo actual
2026-06-17 feat(runoff) : agrego interrución y tarea ONN/OFF
2026-06-17 Se sube firmware, PCB y esquematico
2026-06-17 Segunda entrega firmware pcb y esquematico
2026-06-17 subo codigo
2026-06-17 docs(pcb): se agrega esquemático
2026-06-17 entrega 2
2026-06-17 docs: agrego informe preliminar
2026-06-18 feat: consigna ega
2026-06-18 commit nuevo
2026-06-18 Tareas guardianas, Caceres-Gutierrez
2026-06-18 encoder controlando pwm con tarea guardiana
2026-06-18 Estructura de codigo para informe final
2026-06-19 feat: add mcp4725 test
2026-06-19 actualizar esquemático y layout PCB
2026-06-21 armar pantallas de config y barrido
2026-06-21 agregar teclado numerico
2026-06-21 agregar queue_menu_events y queue_display
2026-06-21 conectar config de pantalla y UART a menu_config con validacion
2026-06-21 actualización PCB y esquemático
2026-06-21 actualizar diagrama de tareas
2026-06-22 code: agrego tareas encoder, oled y eeprom
2026-06-22 Mejora de código, integración de tareas.
2026-06-23 Agrego informe final.
2026-06-23 Actualizo Informe Final.pdf con estructura del firmware
2026-06-23 Docs: informe
    Se carga version actualizada del informe
2026-06-23 Docs: informe
    se carga version actualizada de informe
2026-06-23 Fix: diagrama en bloques
    se agrega sck en ADC y se cambia SCK por BCK
2026-06-23 Fix: diagrama de bloques
    se agrega SCK en ADC y se cambia SCK por BCK
2026-06-23 feat: workspace ecualizador
    se añade el workspace del proyecto
2026-06-23 fix: workspace
    se sube la carpeta correcta, versión equivocada en feat anterior
2026-06-23 Corrección de repositorio.
2026-06-23 Corrección de repositorio.
2026-06-23 Subiendo PCB y esquematico
2026-06-24 task_uart como tarea guardiana del puerto UART
2026-06-24 corregir decimales de kHz y unidad de asentamiento en lcd_display
2026-06-24 validar configuracion de conjunto al iniciar barrido y mostrar popup de error, UART solo RX comandos / TX datos de medicion
2026-06-24 chore: ignorar backup y cache de SquareLine Studio
2026-06-24 feat: implementar medicion del barrido en task_sweep
2026-06-24 Actualizando codigo
2026-06-24 Actualizando diagrama en bloques
2026-06-24 Subiendo informe final
2026-06-24 feat: graficar el barrido en pantalla y enviar puntos por UART
2026-06-24 actualizar diagrama para tener tarea guardiana de UART
2026-06-24 Cambiar operacional por el TL072
2026-06-24 Actualizando PCB, esquematico e informe
2026-06-24 actualizaciones y PCB
2026-06-24 docs(informe): agrego informe ega
2026-06-25 Se sube informe final
2026-06-25 actualizar informe
2026-06-27 feat(flash): agrego componente flash
2026-06-27 feat(lcd): agrego componente lcd
2026-06-27 feat(teclado): agrego componente teclado
2026-06-28 fix: evitar log10(0) en la medicion y fijar escala dB para el grafico
2026-06-28 fix: mejora visual de decimales en esala de frecuencia y ampliar limite de tiempo de asentamiento
2026-06-28 feat: componentes y display tft
2026-06-28 feat: maquina de estados en menu_config
2026-06-28 feat: implementar task_user_controls para botones fisicos BTN1/BTN2
2026-06-29 feat: agregar mensajes de error para el usuario
2026-06-29 fix: error en cola
2026-06-29 actualizar Proyecto SquareLine Studio
2026-06-29 fix Diagrama de Tareas
    Se reemplaza el diagrama de tareas ajustado al main final
2026-06-29 Fix: diagrama de tareas
    se reemplaza diagrama de tareas ajustado a app main final
2026-06-29 Fix Informe
    Se carga la ultima revision del informe
2026-06-29 Fix: informe
    se carga la última revisión del informe
2026-06-29 docs Resolucion Cuestionario
    Se añade la resolucion del cuestionario
2026-06-29 Docs: cuestionario
    se añade la resolucion del cuestionario
2026-06-29 feat main
    Se sube ultima version funcional del main
2026-06-29 Feat: main
    se sube ultima version funcional del main
2026-06-29 docs esquema y pcb
    Se añade el circuito esquematico y el diseño de pcb
2026-06-29 Docs: esquematico y pcb
    se añaden esquematico y pcb del circuito
2026-06-29 Docs: anexos
    se adjuntan anexos como video funcionando, fotos y manual de usuario
2026-06-29 docs anexos
    Se añaden los anexos correspondientes. Renders 3d, Video Funcionando, Ensamble Final, y manual de usuario
2026-06-29 feat: guardar y cargar configuracion del barrido en NVS
2026-06-29 feat: implementar comandos start pause y cancel en UART
2026-06-29 fix: no enviar valores repetidos por uart
2026-06-29 docs: agrego proyecto kicad
2026-06-29 Entrega final.
2026-06-29 Corrección.
2026-06-30 entrega EGA1
2026-06-30 refactor: manejar debounce de botones con reset de queue_btn_isr en vez de gpio_intr_disable/enable
2026-06-30 feat: prioridad de lvgl igual que lcd_display en forma explicita
2026-06-30 fix: encender backlight despues de armar la UI
2026-06-30 docs: actualizar diagrama de tareas
2026-06-30 docs: actualizar valores de componentes
2026-06-30 actualizar valores de componentes
